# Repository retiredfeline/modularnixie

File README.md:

# Modular nixie board

These are the Kicad design files for the [Modular nixie project at Hackaday](https://hackaday.io/project/188427-modularnixie).

## Versioning

First release November 2022

## Notes

The minimum lines required to use this board are: GND, SER (data), SRCLK (shift), RCLK (strobe) and power for the shift register 74HC595 and the nixie. The shift register lines are designed to cascade for multiple digits. The hardware configuration calls for the least significant digit to be shifted in first.

## Authors

* **Ken Yap**

## License

See the [LICENSE](LICENSE.md) file for license rights and limitations (MIT).

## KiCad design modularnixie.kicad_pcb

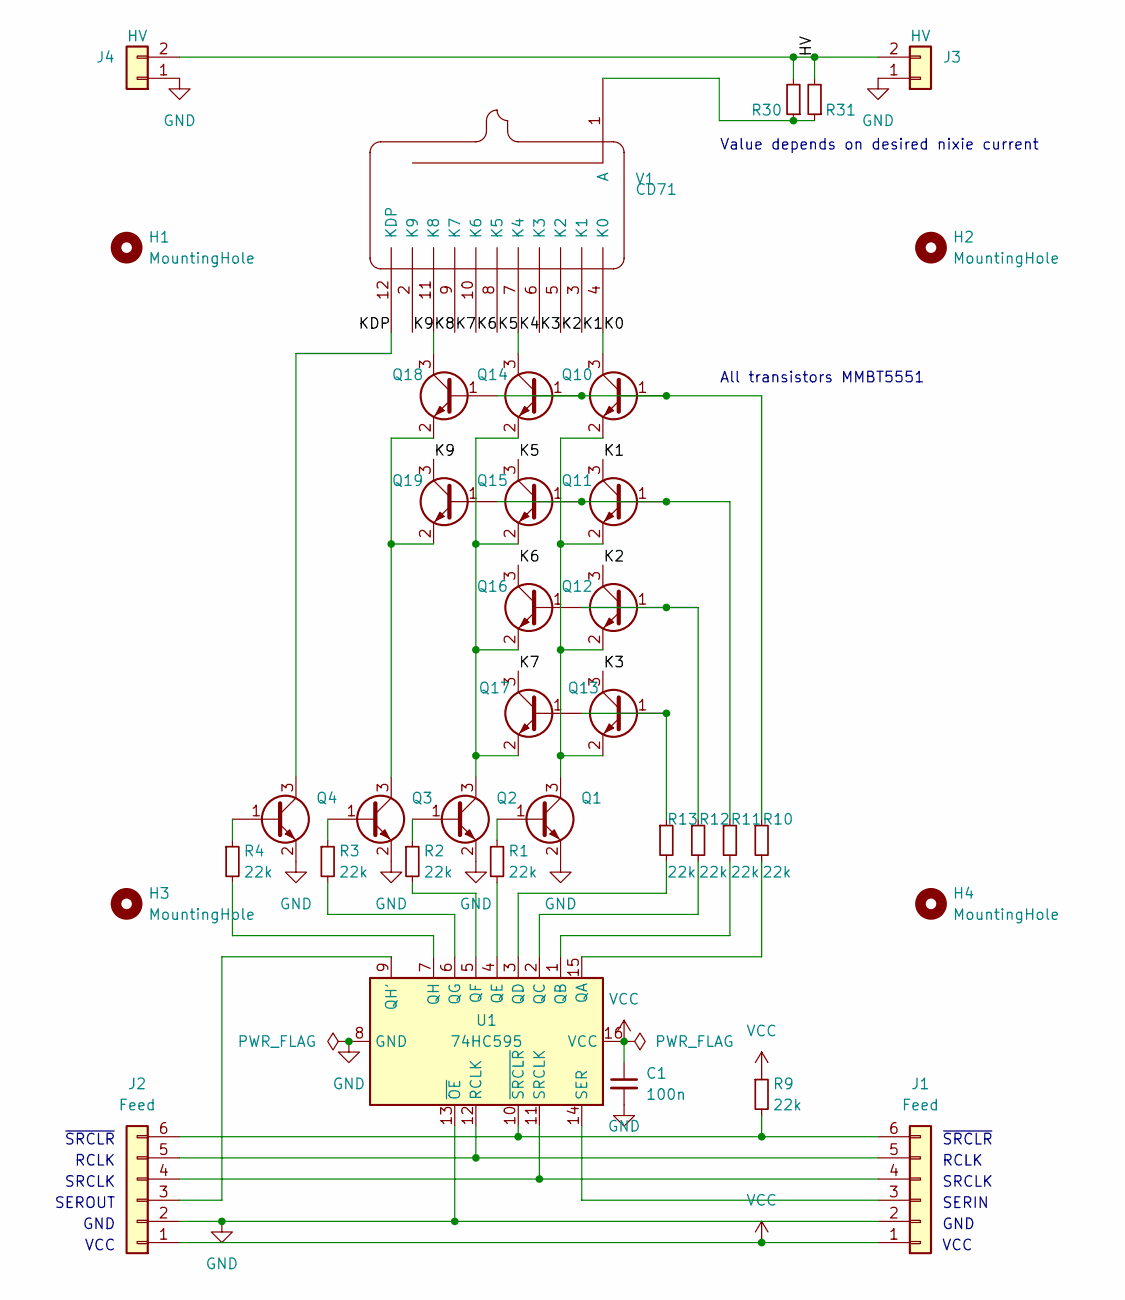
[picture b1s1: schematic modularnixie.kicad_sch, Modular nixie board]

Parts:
C1: 100n; C_0603_1608Metric; LCSC C14663
H1, H2, H3, H4: MountingHole; MountingHole_3.2mm_M3
J1, J2: Feed; PinHeader_1x06_P2.54mm_Vertical
J3, J4: HV; PinHeader_1x02_P2.54mm_Vertical
Q1, Q2, Q3, Q4, Q10, Q11, Q12, Q13, Q14, Q15, Q16, Q17, Q18, Q19: MMBT5551; SOT-23; LCSC C2145
R1, R2, R3, R4, R9, R10, R11, R12, R13: 22k; R_0603_1608Metric; LCSC C31850
R30, R31: R_Axial_DIN0207_L6.3mm_D2.5mm_P15.24mm_Horizontal
U1: 74HC595; SOIC-16_3.9x9.9mm_P1.27mm; LCSC C5947
V1: CD71

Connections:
/HV: J3.2, J4.2, R30.2, R31.2
/K0: Q10.3 (C), V1.4 (K0)
/K1: Q11.3 (C), V1.3 (K1)
/K2: Q12.3 (C), V1.5 (K2)
/K3: Q13.3 (C), V1.6 (K3)
/K4: Q14.3 (C), V1.7 (K4)
/K5: Q15.3 (C), V1.8 (K5)
/K6: Q16.3 (C), V1.10 (K6)
/K7: Q17.3 (C), V1.9 (K7)
/K8: Q18.3 (C), V1.11 (K8)
/K9: Q19.3 (C), V1.2 (K9)
/KDP: Q4.3 (C), V1.12 (KDP)
GND: C1.2, J1.2, J2.2, J3.1, J4.1, Q1.2 (E), Q2.2 (E), Q3.2 (E), Q4.2 (E), U1.8 (GND), U1.13 (~OE)
unnamed: J1.3, U1.14 (SER)
unnamed: J1.4, J2.4, U1.11 (SRCLK)
unnamed: J1.5, J2.5, U1.12 (RCLK)
unnamed: J1.6, J2.6, R9.2, U1.10 (~SRCLR)
unnamed: J2.3, U1.9 (QH')
unnamed: Q1.1 (B), R1.1
unnamed: Q1.3 (C), Q10.2 (E), Q11.2 (E), Q12.2 (E), Q13.2 (E)
unnamed: Q2.1 (B), R2.1
unnamed: Q3.1 (B), R3.1
unnamed: Q4.1 (B), R4.1
unnamed: Q10.1 (B), Q14.1 (B), Q18.1 (B), R10.1
unnamed: Q11.1 (B), Q15.1 (B), Q19.1 (B), R11.1
unnamed: Q12.1 (B), Q16.1 (B), R12.1
unnamed: Q13.1 (B), Q17.1 (B), R13.1
unnamed: Q2.3 (C), Q14.2 (E), Q15.2 (E), Q16.2 (E), Q17.2 (E)
unnamed: Q3.3 (C), Q18.2 (E), Q19.2 (E)
unnamed: R1.2, U1.4 (QE)
unnamed: R2.2, U1.5 (QF)
unnamed: R3.2, U1.6 (QG)
unnamed: R4.2, U1.7 (QH)
unnamed: R10.2, U1.15 (QA)
unnamed: R11.2, U1.1 (QB)
unnamed: R12.2, U1.2 (QC)
unnamed: R13.2, U1.3 (QD)
unnamed: R30.1, R31.1, V1.1 (A)
VCC: C1.1, J1.1, J2.1, R9.1, U1.16 (VCC)

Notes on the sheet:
RCLK
GND
SRCLK
VCC
SERIN
All transistors MMBT5551
Value depends on desired nixie current
SEROUT
~{SRCLR}

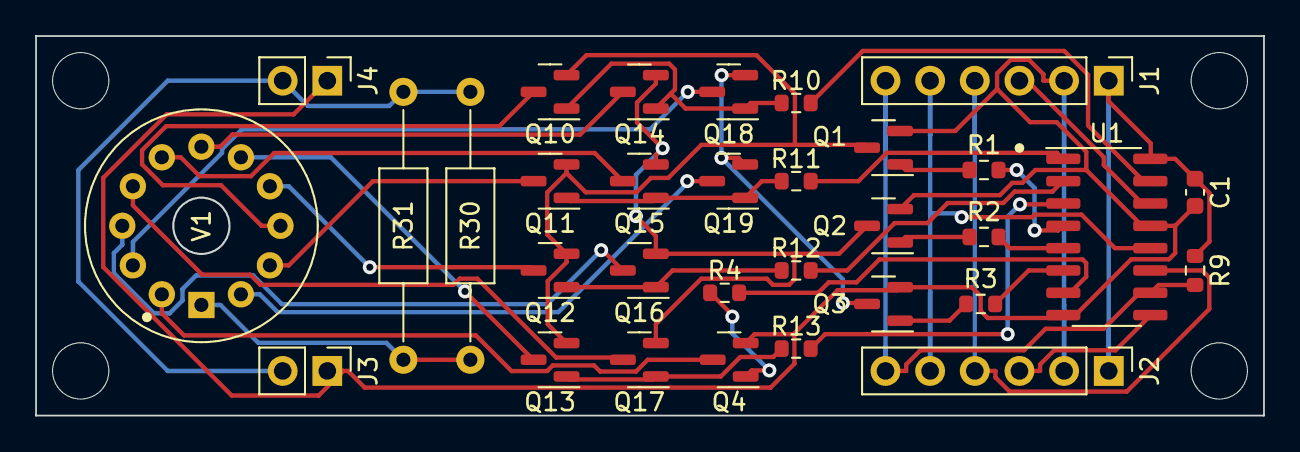
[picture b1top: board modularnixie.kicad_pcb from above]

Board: 2 copper layers, 69.8 x 21.6 mm, 36 parts (0 on the bottom side), 39 nets.

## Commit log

2022-07-20 First release
2022-07-20 Hide pinheaders for 3D rendering as normally wire links will be used
2022-09-26 Stray wire, transistor type typo
2022-10-08 Replace SOP-16 with SOIC-16 to get 3D model, replace modularnixie.jpg with front and back screenshots
2022-10-10 Actually replace SOP-16 with SOIC-16 to get 3D model
2022-12-20 Tidy placement of mounting hole symbol
2023-01-08 Add datasheet
